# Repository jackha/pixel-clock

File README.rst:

Pixel Clock
-----------

.. image:: images/IMG_3512.JPG

A pixel clock with an 8x8 rgb led display based on Arduino.

- Atmega 328 microcontroller
- DS3231 realtime clock module
- ws2812 8x8 LED display aka NeoPixel.
- Control using a rotary encoder /w button.

The case consist of a front and a back part. It is modeled in OpenSCAD.

The pcb is designed in Eagle.

All is work in progress. You can follow the project:

http://jh-interact.blogspot.nl/

http://www.thingiverse.com/thing:1372109

Arduino dependencies
--------------------

Tested and working with these libraries. Many thanks to the authors
for creating and sharing them!!

- Sodaq_DS3231 by keestux, 1.2.0

- Adafruit NeoPixel 1.0.4

- Adafruit GFX Library 1.1.4

- Encoder by Paul Stoffregen 1.4.0

License
-------

Open source hardware and software :-) Please follow my License as I put time
and effort in this project. Thanks!

https://creativecommons.org/licenses/by-nc/3.0/
Attribution-NonCommercial 3.0 Unported (CC BY-NC 3.0)

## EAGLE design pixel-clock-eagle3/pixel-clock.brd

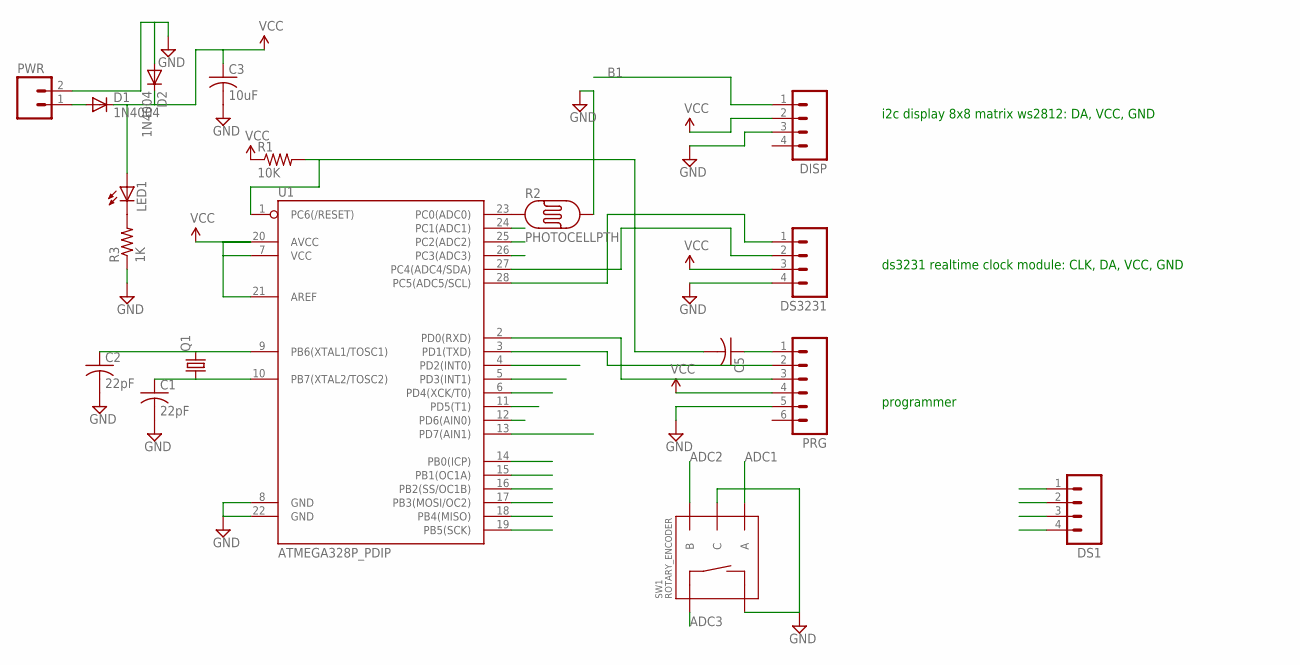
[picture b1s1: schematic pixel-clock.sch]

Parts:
C1, C2: 22pF; C050-024X044
C3: 10uF; C025-025X050
C5: C-US025-025X050; C025-025X050
D1, D2: 1N4004; DO41-10
DISP: M04PTH; 1X04
DS1, DS3231: M04PTH; 1X04
LED1: LED3MM
PRG: M06SILK_FEMALE_PTH; 1X06
PWR: M02PTH3; 1X02_LONGPADS
Q1: CRYSTALHC49S; HC49/S
R1: 10K; 0207/9
R2: PHOTOCELLPTH; PHOTOCELL
R3: 1K; 0207/9
SW1: ROTARY_ENCODER; ROTARY_ENC_PLAIN
U1: ATMEGA328P_PDIP; DIL28-3

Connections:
ADC1: SW1.A, U1.24 (PC1(ADC1))
ADC2: SW1.B, U1.25 (PC2(ADC2))
ADC3: SW1.SW+, U1.26 (PC3(ADC3))
B0: DS1.1, U1.14 (PB0(ICP))
B1: DISP.1, U1.15 (PB1(OC1A))
B2: U1.16 (PB2(SS/OC1B))
B3: U1.17 (PB3(MOSI/OC2))
B4: U1.18 (PB4(MISO))
B5: U1.19 (PB5(SCK))
D0: PRG.3, U1.2 (PD0(RXD))
D1: PRG.2, U1.3 (PD1(TXD))
D2: U1.4 (PD2(INT0))
D3: U1.5 (PD3(INT1))
D4: U1.6 (PD4(XCK/T0))
D5: U1.11 (PD5(T1))
D6: DS1.3, U1.12 (PD6(AIN0))
D7: DS1.2, U1.13 (PD7(AIN1))
GND: C1.2, C2.2, C3.2, D2.A, DISP.3, DS1.4, DS3231.4, PRG.5, PWR.2, R2.2, R3.1, SW1.C, SW1.SW-, U1.8 (GND), U1.22 (GND)
unnamed: DS3231.1, U1.28 (PC5(ADC5/SCL))
unnamed: DS3231.2, U1.27 (PC4(ADC4/SDA))
unnamed: R2.1, U1.23 (PC0(ADC0))
unnamed: C2.1, Q1.2, U1.9 (PB6(XTAL1/TOSC1))
unnamed: C1.1, Q1.1, U1.10 (PB7(XTAL2/TOSC2))
unnamed: D1.A, PWR.1
unnamed: LED1.K (C), R3.2
unnamed: C5.1, PRG.1
unnamed: C5.2, R1.2, U1.1 (PC6(/RESET))
VCC: C3.1, D1.C, D2.C, DISP.2, DS3231.3, LED1.A, PRG.4, R1.1, U1.7 (VCC), U1.20 (AVCC), U1.21 (AREF)

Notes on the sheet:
i2c display 8x8 matrix ws2812: DA, VCC, GND
ds3231 realtime clock module: CLK, DA, VCC, GND
programmer

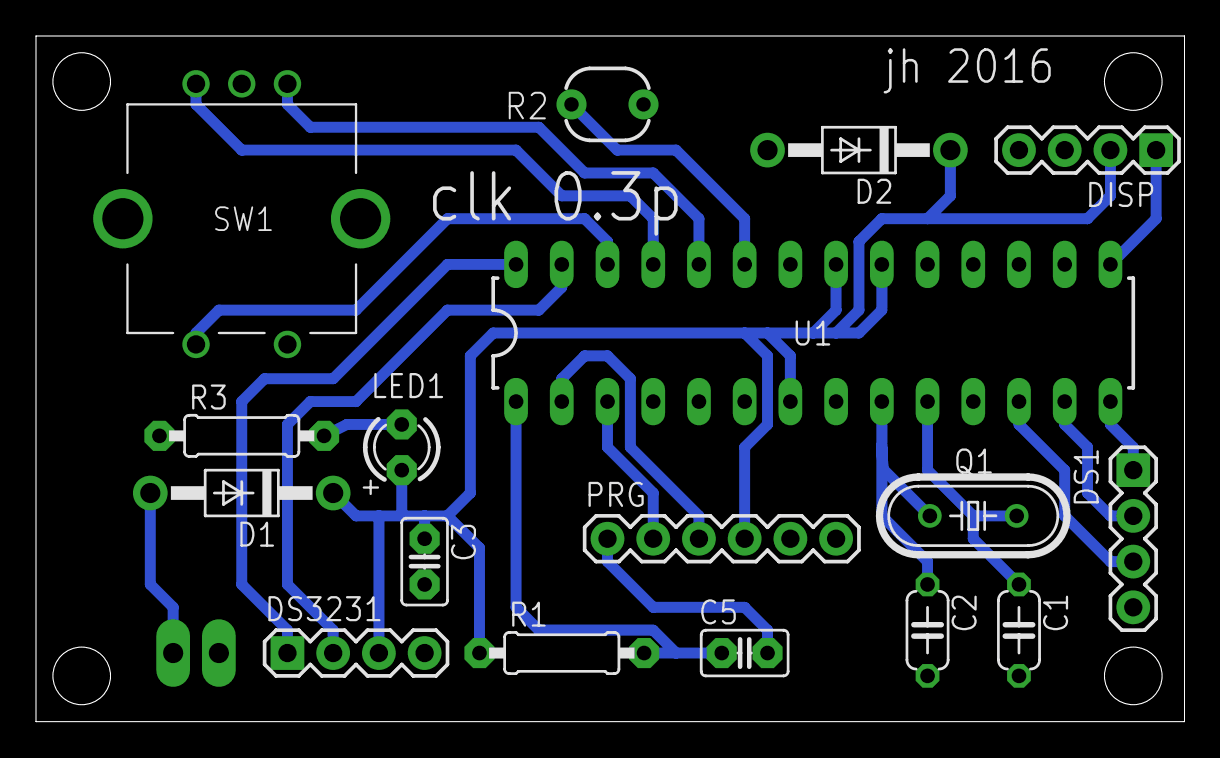
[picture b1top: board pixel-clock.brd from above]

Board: 2 copper layers, 63.8 x 38.1 mm, 18 parts (0 on the bottom side), 20 nets.

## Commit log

2016-02-16 first
2016-02-16 first readme
2016-02-16 readme
2016-02-17 added colors
2016-02-24 better set clock, more clock options
2016-02-25 better color selection, better party mode
2016-02-25 eeprom + changes
2016-02-25 reverse color assign
2016-02-25 moved arduino stuff to arduino subdir
2016-02-25 added openscad and eagle
2016-02-26 added links in readme
2016-02-26 image
2016-02-26 images
2016-03-02 added experimental game of life
2016-03-04 added 4x4 mode, better game of life, better color selecting using hue/saturation
2016-03-11 adjust colors
2016-03-13 added case 4b
2016-03-13 added knob.scad
2016-03-14 added dependencies in readme
2016-03-14 Added first word clock case
2016-03-19 Split bitmaps and fonts into separate header files
2016-03-22 implemented colorful dutch word clock
2016-03-22 colors not overflowing
2016-03-25 yay robot mode
2016-04-04 added brightness program mode, return to default mode after 5 min of inactivity
2016-04-04 now really reset program mode after 5 min
2016-04-12 splitted tables, fonts and bitmap
2016-04-12 splitted some big parts
2016-04-12 busy with tetris ooh yeah
2016-04-25 mode images are now always visible (almost) independent of brightness

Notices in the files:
parts and their libraries:
SparkFun-Connectors: Licensing: Creative Commons ShareAlike 4.0 International - https://creativecommons.org/licenses/by-sa/4.0
